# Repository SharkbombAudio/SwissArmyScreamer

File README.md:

# SwissArmyScreamer
The SuperScreamer - It’s the best of all 3 of your favorite tube screamer pedals. All in one. With analog switching. Not much more you can ask for.  TS808, TS9, and TS10.

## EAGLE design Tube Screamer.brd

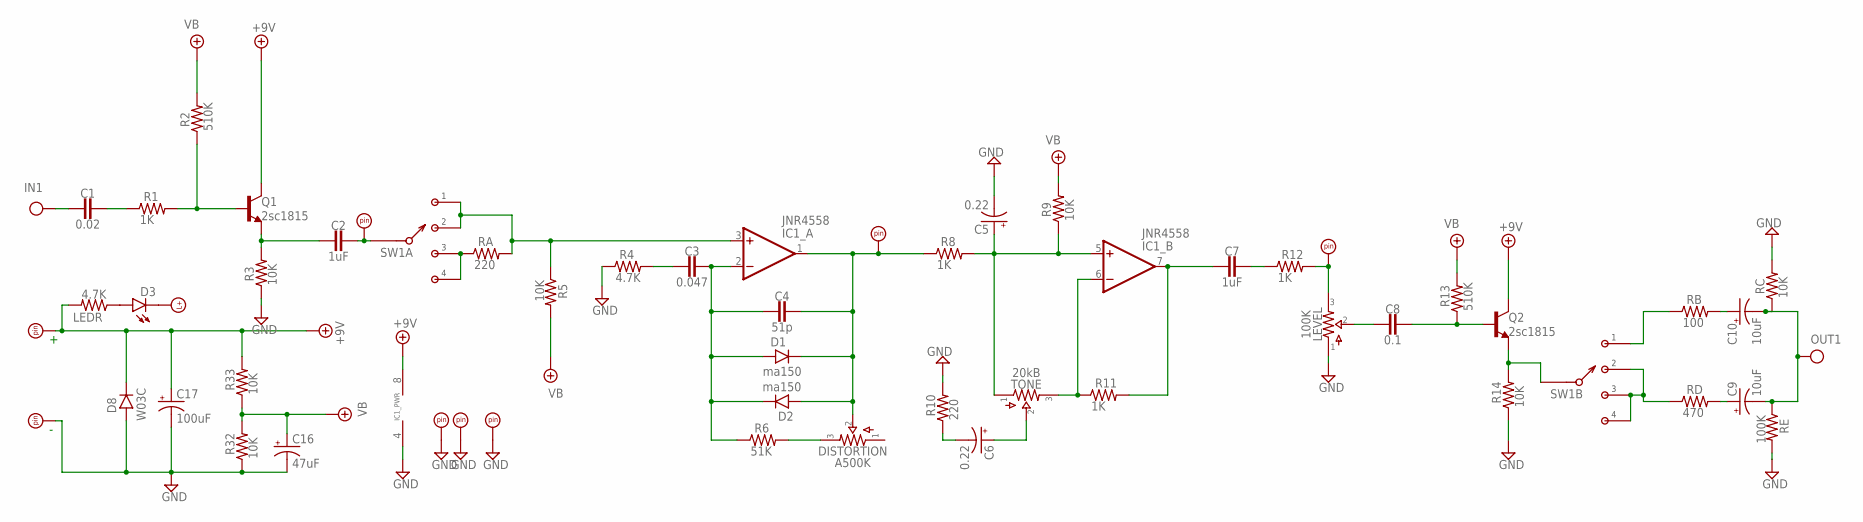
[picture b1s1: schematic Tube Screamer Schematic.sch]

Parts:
C1: 0.02; 0.2".MED
C2, C7: 1uF; 0.2".LRG
C3: 0.047; 0.2".MED
C4: 51p; 0.2".MED
C5, C6: 0.22; 050_020_1
C8: 0.1; 0.2".MED
C9, C10: 10uF; 050_020_1
C16: 47uF; 050_020_1
C17: 100uF; 050_020_1
D1, D2: ma150; DO41-3
D3: LED3MM
D8: W03C; DO35-3
DISTORTION: A500K; 16MM_B.MOUNT
IC1: JNR4558; DIL08
IN1: IN; SQUARE
LEDR: 4.7K; R0207/3
LEVEL: 100K; 16MM_B.MOUNT
OUT1: OUT; SQUARE
Q1, Q2: 2sc1815; TO92
R1, R8, R11, R12: 1K; R0207/3
R2, R13: 510K; R0207/3
R3, R5, R9, R14, R32, R33: 10K; R0207/3
R4: 4.7K; R0207/3
R6: 51K; R0207/3
R10: 220; R0207/3
RA: 220; R0207/3
RB: 100; R0207/3
RC: 10K; R0207/3
RD: 470; R0207/3
RE: 100K; R0207/3
SW1: 2P4TMINIROTARY; 2P4T.MINI
TONE: 20kB; 16MM_B.MOUNT
U$1, U$2, U$3, U$4, U$5, U$6, U$8, U$9: PADS.RND_NL; PAD2
U$7: LED+; SQUARE

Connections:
+9V: C17.+, D8.C, IC1.8 (V+), LEDR.2, Q1.2 (C), Q2.2 (C), R33.2, U$1.P$1
GND: C5.-, C16.-, C17.-, D8.A, IC1.4 (V-), LEVEL.1, R3.1, R4.1, R10.2, R14.1, R32.1, RC.2, RE.2, U$2.P$1, U$3.P$1, U$4.P$1, U$5.P$1
IN: C1.2, IN1.1
unnamed: C1.1, R1.1
unnamed: Q1.1 (B), R1.2, R2.1
unnamed: C2.1, SW1.A, U$6.P$1
unnamed: C2.2, Q1.3 (E), R3.2
unnamed: RA.1, SW1.A3 (3), SW1.A4 (4)
unnamed: IC1.3 (+IN), R5.1, RA.2, SW1.A1 (1), SW1.A2 (2)
unnamed: RD.1, SW1.B2 (2), SW1.B3 (3), SW1.B4 (4)
unnamed: C3.1, C4.2, D1.A, D2.C, IC1.2 (-IN), R6.1
unnamed: C3.2, R4.2
unnamed: C4.1, D1.C, D2.A, DISTORTION.2, IC1.1 (OUT), R8.1, U$8.P$1
unnamed: DISTORTION.3, R6.2
unnamed: C5.+, IC1.5 (+IN), R8.2, R9.1, TONE.1
unnamed: IC1.6 (-IN), R11.1, TONE.3
unnamed: C7.2, IC1.7 (OUT), R11.2
unnamed: C6.+, TONE.2
unnamed: C6.-, R10.1
unnamed: C7.1, R12.1
unnamed: LEVEL.3, R12.2, U$9.P$1
unnamed: C8.2, LEVEL.2
unnamed: C8.1, Q2.1 (B), R13.1
unnamed: Q2.3 (E), R14.2, SW1.B (A)
unnamed: RB.1, SW1.B1 (1)
unnamed: D3.K (C), U$7.1
unnamed: C9.+, RD.2
unnamed: C10.+, RB.2
unnamed: D3.A, LEDR.1
OUT: C9.-, C10.-, OUT1.1, RC.1, RE.1
VB: C16.+, R2.2, R5.2, R9.2, R13.2, R32.2, R33.1

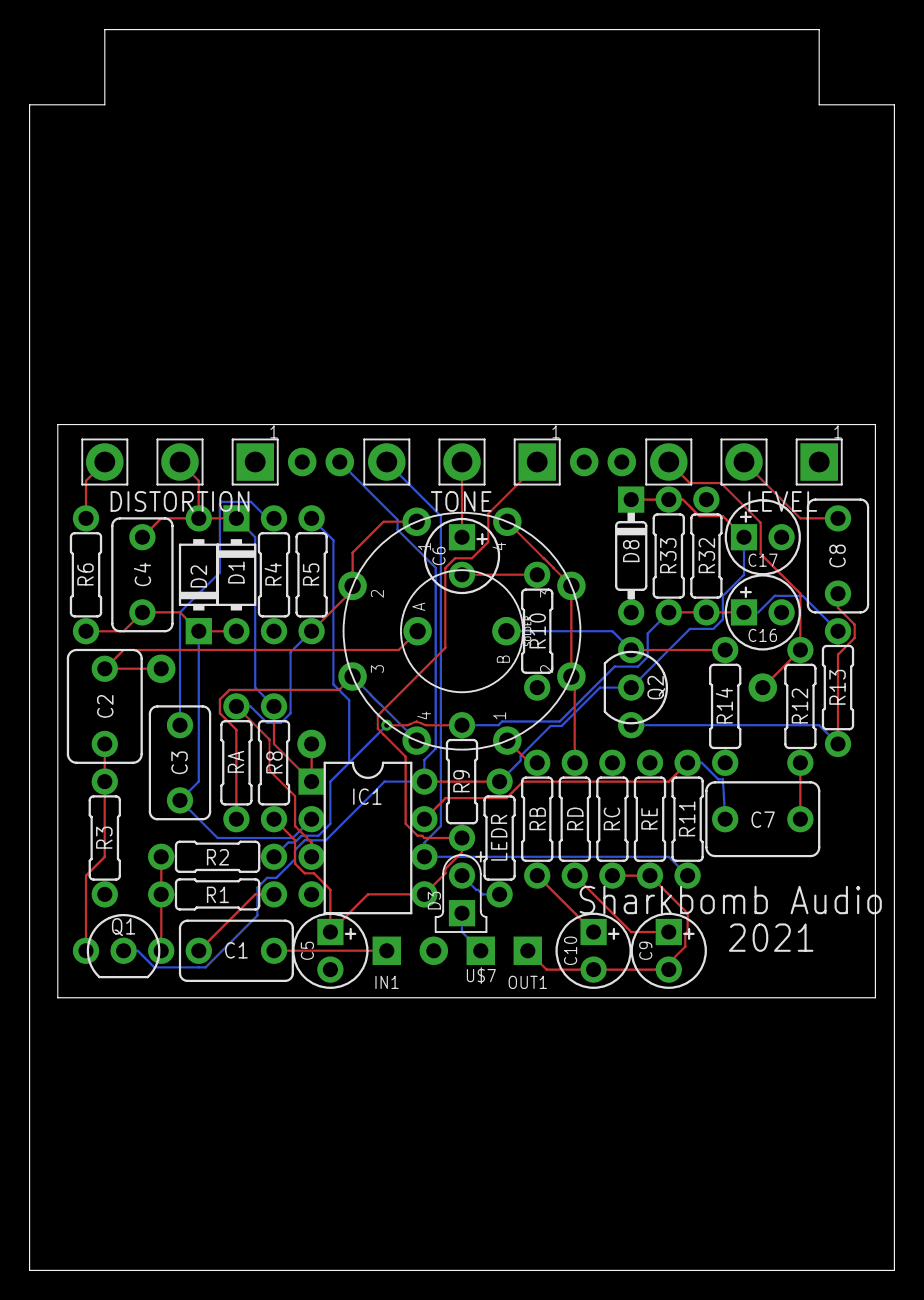
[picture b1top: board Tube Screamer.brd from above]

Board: 2 copper layers, 58.4 x 83.8 mm, 56 parts (0 on the bottom side), 31 nets.

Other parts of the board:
E$1: 125B

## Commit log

2023-02-15 Schematic and board layout for the Screamer
